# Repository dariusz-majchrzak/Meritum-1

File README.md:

# Meritum-1: Polish 8-bit Home Computer
This repository provides all the files needed to build a **Meritum 1 (Model 1)** ( https://pl.wikipedia.org/wiki/Meritum_(komputer) ) hardware recreation, closely following the design of the first microcomputer to be mass‑produced in Poland.<br>

Production of the Meritum computer began in mid‑1983, and its architecture was based on a design similar to the TRS‑80 Model I. Across all versions — Meritum I, II, and III — approximately 2,500 units were produced between 1984 and 1986.<br>

It has fascinated me for years as an important part of Poland’s computing history. I never had the chance to see an original unit in person, and my attempts to buy one at auctions quickly ended with prices far beyond reach. 
I also noticed that almost no modern retro‑computing projects related to it exist.

Given that, I decided to build one myself: using the documentation available online — schematics, module descriptions, and board photos — I set out to recreate the machine as my own hardware project.

**Meritum 1 (Model 1)** <br>
Basic Technical Specifications:
* RAM: 16 KB (RAMD) + 1 KB (RAMS)
* ROM: 14 KB (BASIC)
* Video Memory: 1 KB (RAMS)
* Display Modes: Text — 16×64 or 16×32
* Peripherals: serial interface (i8251), parallel interface (i8255), tape interface
* Colors: Monochrome
<br>
As of September 27, 2026, there are 4 successful builds (based on this pcb project), so the design files can be assumed valid.<br>
<br>

Top view of the mainboard:<br>

Side view of the computer with connectors:<br>

Example startup screen:<br>

Important notes:<br>
* Please note that this is a complex hardware project that requires solid technical expertise from anyone who decides to build it.<br>
* While significant care has been taken during the design and verification process, the project may still need additional fixes, especially if the original design included fixes implemented directly at the PCB level that were not reflected in the published schematics.

## PCBs
The clone consists of two separate PCBs:
* [Meritum_PGW](Meritum_PGW) (Meritum Płyta Główna) - is the main board.
* [Meritum_KLT](Meritum_KLT) (Meritum Klawiatura) - is a replacement keyboard that uses standard Cherry MX switches.

## ROMs
Since the licensing status of the ROMs used in the Meritum 1 computer is not clear to me, I have not included them in this repository.<br> 
Below, however, I provide links to a websites where they can be found, along with many other valuable resources:
* https://web.archive.org/web/20201023154655/https://sites.google.com/site/krzkomar/meritum-1
* https://www.planetemu.net/rom/mame-roms-merged/meritum1<br>
  
Many useful materials can also be found at: https://www.speccy.pl/news.php .

## Assembling
Although the mainboard includes several configuration jumpers, it does not require any additional settings that need to be adjusted before powering it on. The default configuration is sufficient.<br>

To connect mainboard with keyboard I have used:
-  single and double Row, 2.54mm straight, Gold PCB Female Sockets Connector
-  single and double Row, 2.54mm straight, Gold PCB Male Pin Header connector (h=29.5mm)
  
More to follow.

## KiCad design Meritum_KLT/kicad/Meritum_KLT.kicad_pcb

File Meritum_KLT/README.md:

# Meritum 1 - keyboard

This part of the project is the clone of the Meritum 1 keyboard.

## Files
This directory contains: 

* [BOM](bom) - Interactive HTML BOM
* [Gerber](gerber) - files (JLCPCB-compatible zip files)
* [IMG](img) - photos of the keyboard
* [KiCAD](kicad) - project design in KiCAD 10
* [Schematic](schematic) - Schematic in PDF format

## Assembling
As for assembling the keyboard PCB, there are no major challenges here. The board is relatively straightforward to build.<br> 
One piece of information may be more important: for mounting the switches I used gold‑plated hot‑swap sockets for mechanical keyboards.
See: [Meritum1_KLT_BOTTOM](img/Meritum1_KLT_BOTTOM.png)

More to follow.

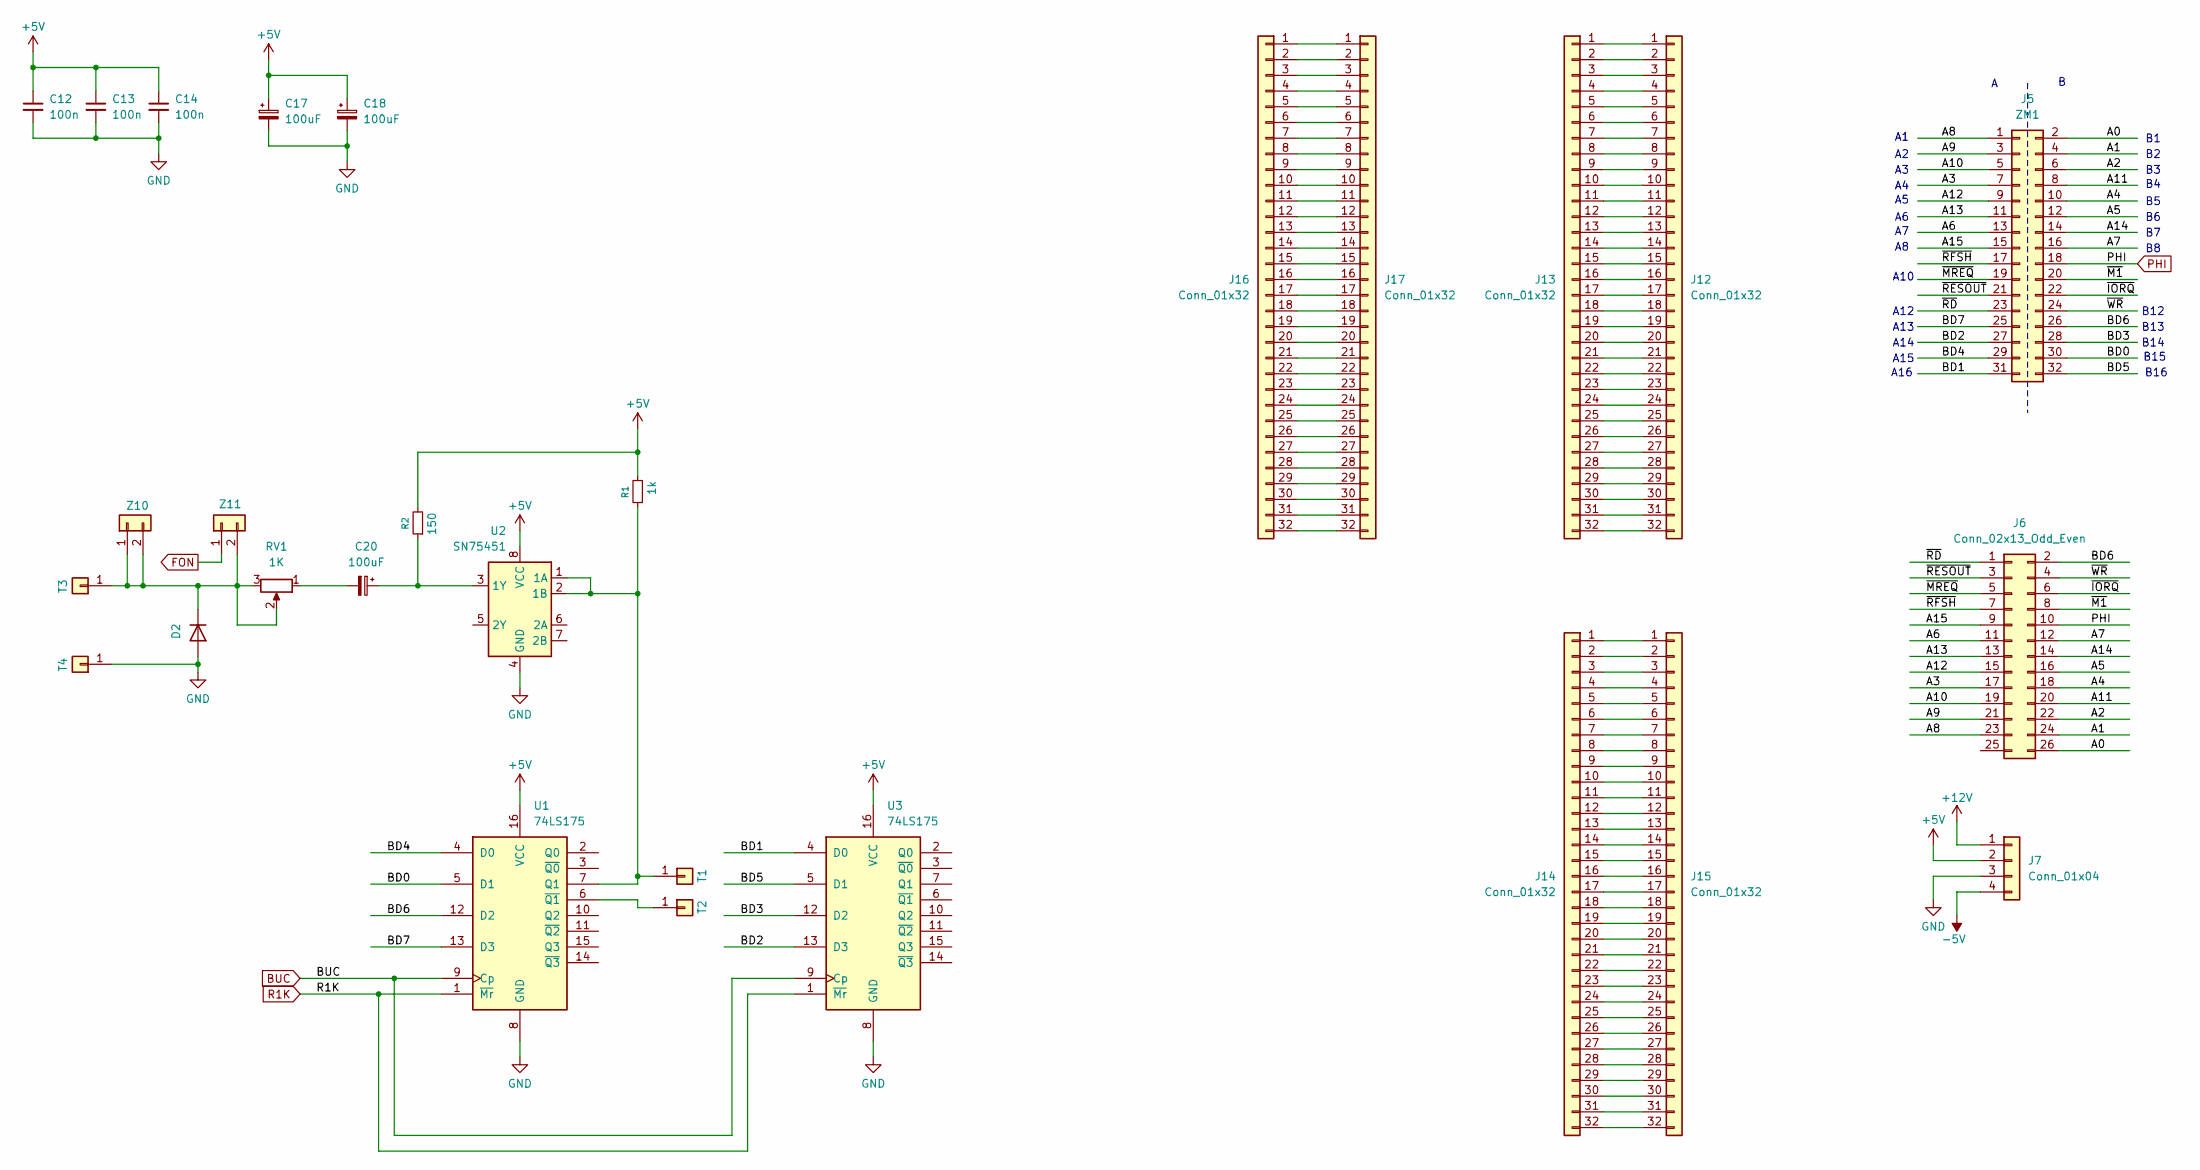
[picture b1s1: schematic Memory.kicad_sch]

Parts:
C12, C13, C14: 100n; C_Rect_L7.0mm_W2.5mm_P5.00mm
C17, C18, C20: 100uF; CP_Radial_D5.0mm_P2.50mm
D2: 1N4148; D_DO-35_SOD27_P7.62mm_Horizontal
J5: ZM1; PinHeader_2x16_P2.54mm_Vertical
J6: Conn_02x13_Odd_Even; PinHeader_2x13_P2.54mm_Vertical
J7: Conn_01x04; PinHeader_1x04_P2.54mm_Vertical
J12, J13, J14, J15, J16, J17: Conn_01x32; PinHeader_1x32_P2.54mm_Vertical
R1: 1k; r_400
R2: 150; r_400
RV1: 1K; Potentiometer_Bourns_3386P_Vertical
T1, T2, T3, T4: T18; pin
U1, U3: 74LS175; DIP-16_W7.62mm_LongPads
U2: SN75451; DIP-8_W7.62mm
Z10, Z11: Conn_01x02; PinHeader_1x02_P2.54mm_Vertical

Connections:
+5V: C12.1, C13.1, C14.1, C17.1, C18.1, J7.2, R1.2, R2.2, U1.16 (VCC), U2.8 (VCC), U3.16 (VCC); also elsewhere on the board
+12V: J7.1; also elsewhere on the board
-5V: J7.4; also elsewhere on the board
/Memory/A0: J5.2, J6.26
/Memory/A1: J5.4, J6.24
/Memory/A2: J5.6, J6.22
/Memory/A3: J5.7, J6.17
/Memory/A4: J5.10, J6.18
/Memory/A5: J5.12, J6.16
/Memory/A6: J5.13, J6.11
/Memory/A7: J5.16, J6.12
/Memory/A8: J5.1, J6.23
/Memory/A9: J5.3, J6.21
/Memory/A10: J5.5, J6.19
/Memory/A11: J5.8, J6.20
/Memory/A12: J5.9, J6.15
/Memory/A13: J5.11, J6.13
/Memory/A14: J5.14, J6.14
/Memory/A15: J5.15, J6.9
/Memory/BD0: J5.30, U1.5 (D1)
/Memory/BD1: J5.31, U3.4 (D0)
/Memory/BD2: J5.27, U3.13 (D3)
/Memory/BD3: J5.28, U3.12 (D2)
/Memory/BD4: J5.29, U1.4 (D0)
/Memory/BD5: J5.32, U3.5 (D1)
/Memory/BD6: J5.26, J6.2, U1.12 (D2)
/Memory/BD7: J5.25, U1.13 (D3)
/Memory/~IORQ: J5.22, J6.6
/Memory/~M1: J5.20, J6.8
/Memory/~MREQ: J5.19, J6.5
/Memory/~RD: J5.23, J6.1
/Memory/~RESOUT: J5.21, J6.3
/Memory/~RFSH: J5.17, J6.7
/Memory/~WR: J5.24, J6.4
BUC: U1.9 (Cp), U3.9 (Cp); also elsewhere on the board
FON: Z11.1; also elsewhere on the board
GND: C12.2, C13.2, C14.2, C17.2, C18.2, D2.2 (A), J7.3, T4.1 (Pin_1_1), U1.8 (GND), U2.4 (GND), U3.8 (GND); also elsewhere on the board
unnamed: C20.2, RV1.1
unnamed: D2.1 (K), RV1.2, RV1.3, T3.1 (Pin_1_1), Z10.1, Z10.2, Z11.2
unnamed: J12.1, J13.1
unnamed: J12.2, J13.2
unnamed: J12.3, J13.3
unnamed: J12.4, J13.4
unnamed: J12.5, J13.5
unnamed: J12.6, J13.6
unnamed: J12.7, J13.7
unnamed: J12.8, J13.8
unnamed: J12.9, J13.9
unnamed: J12.10, J13.10
unnamed: J12.11, J13.11
unnamed: J12.12, J13.12
unnamed: J12.13, J13.13
unnamed: J12.14, J13.14
unnamed: J12.15, J13.15
unnamed: J12.16, J13.16
unnamed: J12.17, J13.17
unnamed: J12.18, J13.18
unnamed: J12.19, J13.19
unnamed: J12.20, J13.20
unnamed: J12.21, J13.21
unnamed: J12.22, J13.22
unnamed: J12.23, J13.23
unnamed: J12.24, J13.24
unnamed: J12.25, J13.25
unnamed: J12.26, J13.26
unnamed: J12.27, J13.27
unnamed: J12.28, J13.28
unnamed: J12.29, J13.29
unnamed: J12.30, J13.30
unnamed: J12.31, J13.31
unnamed: J12.32, J13.32
unnamed: J14.1, J15.1
unnamed: J14.2, J15.2
unnamed: J14.3, J15.3
unnamed: J14.4, J15.4
unnamed: J14.5, J15.5
unnamed: J14.6, J15.6
unnamed: J14.7, J15.7
unnamed: J14.8, J15.8
unnamed: J14.9, J15.9
unnamed: J14.10, J15.10
unnamed: J14.11, J15.11
unnamed: J14.12, J15.12
unnamed: J14.13, J15.13
unnamed: J14.14, J15.14
unnamed: J14.15, J15.15
unnamed: J14.16, J15.16
unnamed: J14.17, J15.17
unnamed: J14.18, J15.18
unnamed: J14.19, J15.19
unnamed: J14.20, J15.20
unnamed: J14.21, J15.21
unnamed: J14.22, J15.22
unnamed: J14.23, J15.23
unnamed: J14.24, J15.24
unnamed: J14.25, J15.25
unnamed: J14.26, J15.26
unnamed: J14.27, J15.27
unnamed: J14.28, J15.28
unnamed: J14.29, J15.29
unnamed: J14.30, J15.30
unnamed: J14.31, J15.31
unnamed: J14.32, J15.32
unnamed: J16.1, J17.1
unnamed: J16.2, J17.2
unnamed: J16.3, J17.3
unnamed: J16.4, J17.4
unnamed: J16.5, J17.5
unnamed: J16.6, J17.6
unnamed: J16.7, J17.7
unnamed: J16.8, J17.8
unnamed: J16.9, J17.9
unnamed: J16.10, J17.10
unnamed: J16.11, J17.11
unnamed: J16.12, J17.12
unnamed: J16.13, J17.13
unnamed: J16.14, J17.14
unnamed: J16.15, J17.15
unnamed: J16.16, J17.16
unnamed: J16.17, J17.17
unnamed: J16.18, J17.18
unnamed: J16.19, J17.19
unnamed: J16.20, J17.20
unnamed: J16.21, J17.21
unnamed: J16.22, J17.22
unnamed: J16.23, J17.23
unnamed: J16.24, J17.24
unnamed: J16.25, J17.25
unnamed: J16.26, J17.26
unnamed: J16.27, J17.27
unnamed: J16.28, J17.28
unnamed: J16.29, J17.29
unnamed: J16.30, J17.30
unnamed: J16.31, J17.31
unnamed: J16.32, J17.32
unnamed: R1.1, T1.1 (Pin_1_1), U1.7 (Q1), U2.1 (1A), U2.2 (1B)
unnamed: T2.1 (Pin_1_1), U1.6 (~Q1)
unnamed: C20.1, R2.1, U2.3 (1Y)
PHI: J5.18, J6.10
R1K: U1.1 (~Mr), U3.1 (~Mr); also elsewhere on the board

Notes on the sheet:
B13
B12
A16
B15
A15
B16
A14
A13
A10
A12
B14

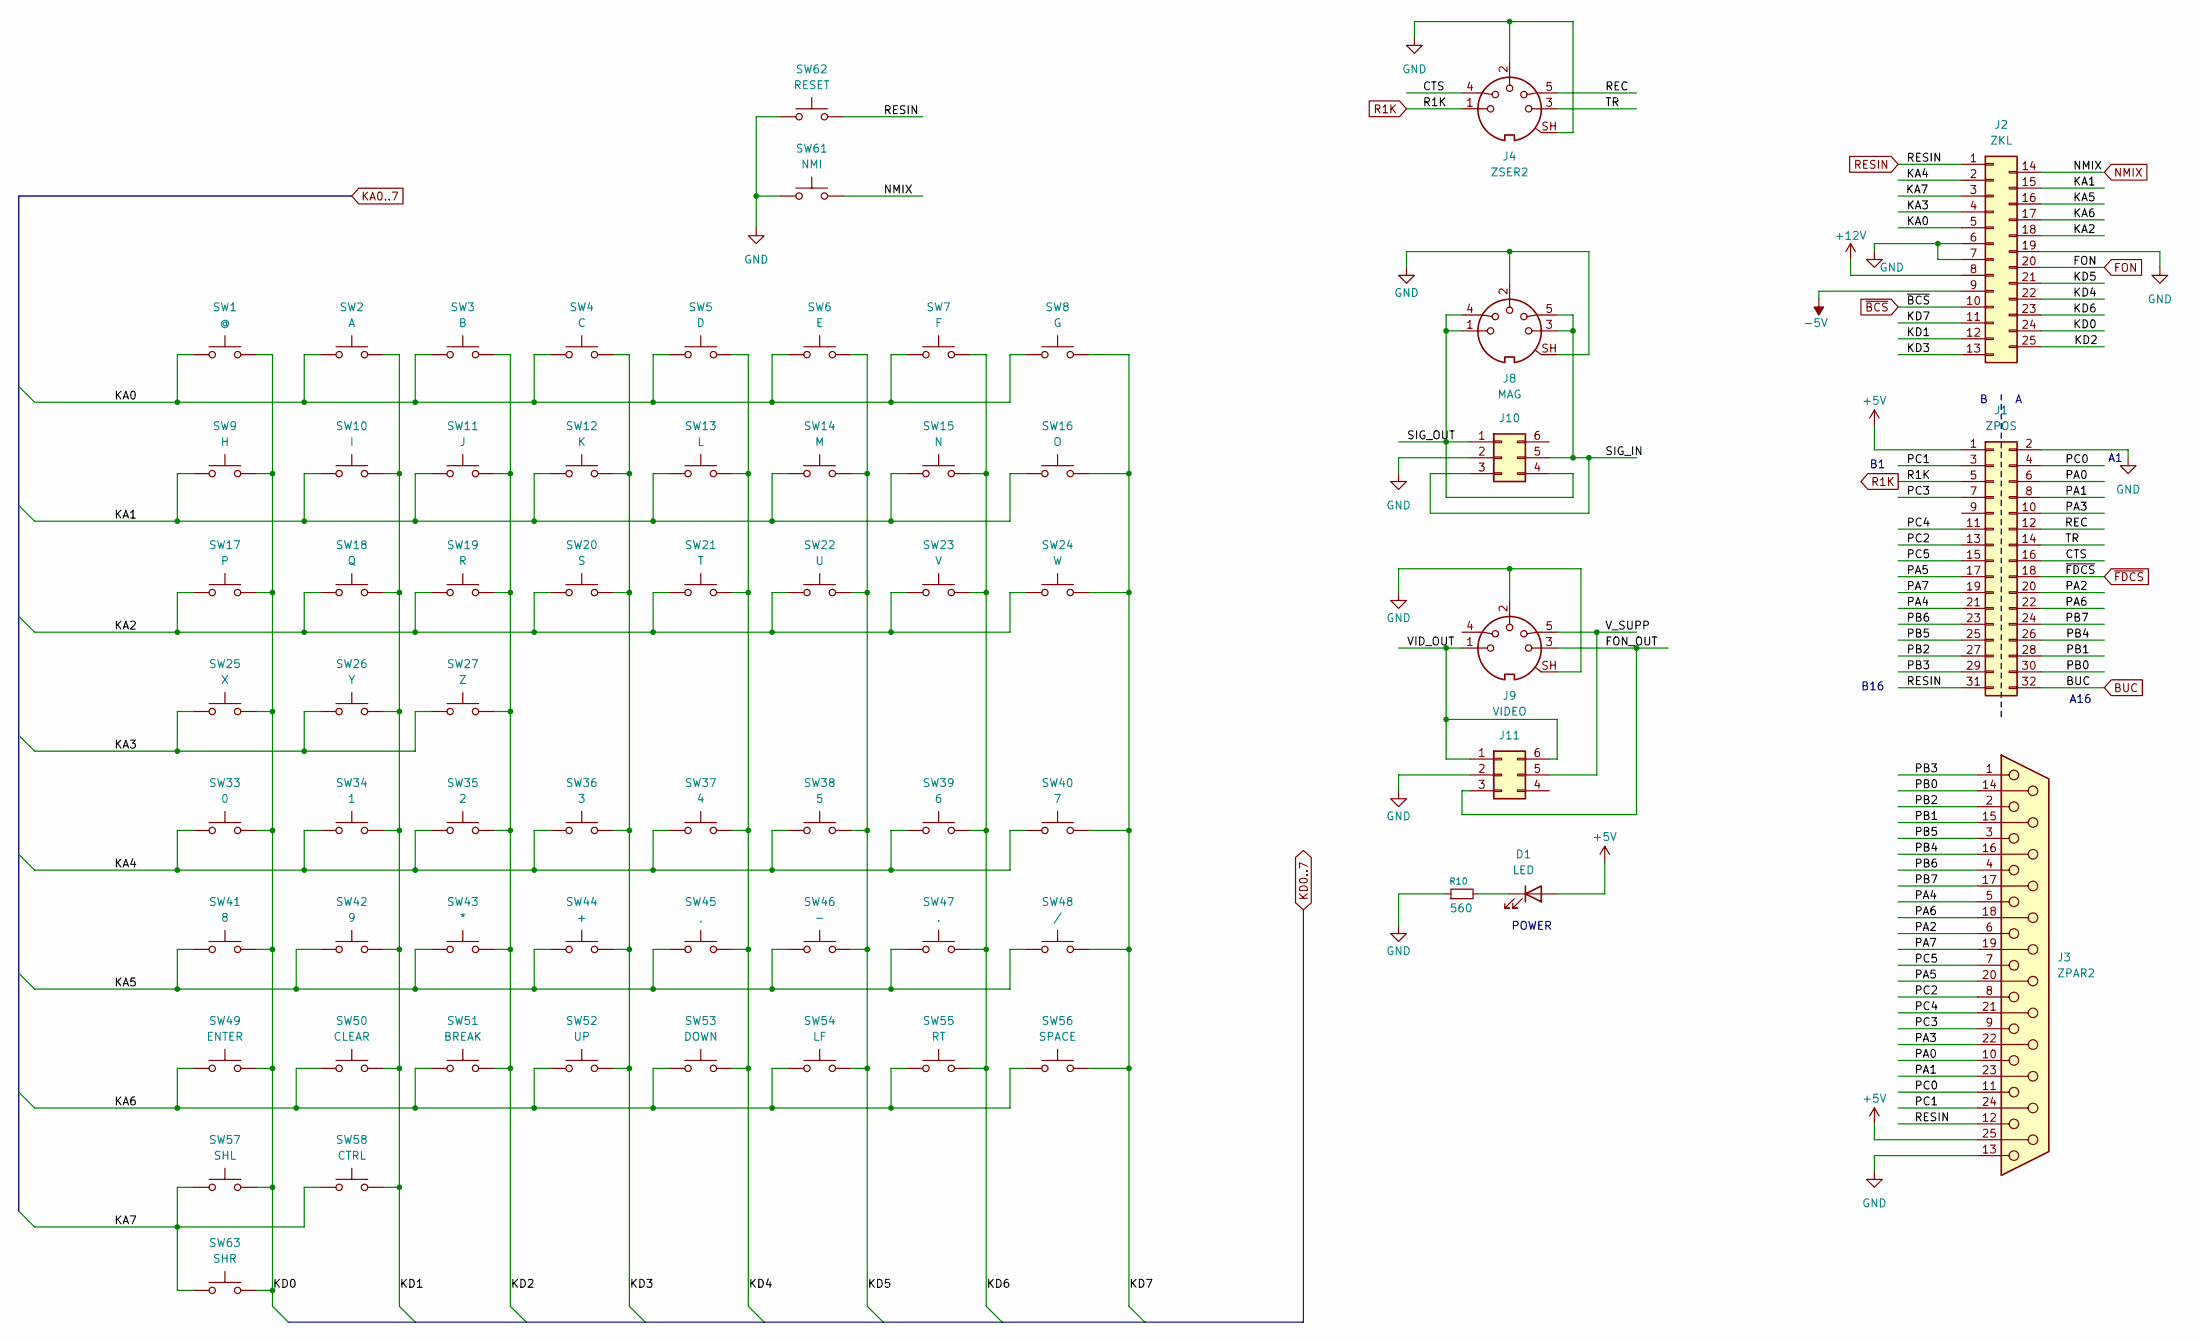
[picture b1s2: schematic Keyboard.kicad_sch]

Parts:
D1: LED; LED_D5.0mm
J1: ZPOS; PinHeader_2x16_P2.54mm_Vertical
J2: ZKL; PinSocket_25_P2.54mm_Vertical
J3: ZPAR2; DSUB-25_Socket_Horizontal_P2.77x2.84mm_EdgePinOffset7.70mm_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
J4: ZSER2; CUI_SDS-50J
J8: MAG; CUI_SDS-50J
J9: VIDEO; CUI_SDS-50J
J10, J11: Conn_02x03_Counter_Clockwise; PinHeader_2x03_P2.54mm_Vertical
R10: 560; r_400
SW1: @; SW_Cherry_MX_1.00u_PCB
SW2: A; SW_Cherry_MX_1.00u_PCB
SW3: B; SW_Cherry_MX_1.00u_PCB
SW4: C; SW_Cherry_MX_1.00u_PCB
SW5: D; SW_Cherry_MX_1.00u_PCB
SW6: E; SW_Cherry_MX_1.00u_PCB
SW7: F; SW_Cherry_MX_1.00u_PCB
SW8: G; SW_Cherry_MX_1.00u_PCB
SW9: H; SW_Cherry_MX_1.00u_PCB
SW10: I; SW_Cherry_MX_1.00u_PCB
SW11: J; SW_Cherry_MX_1.00u_PCB
SW12: K; SW_Cherry_MX_1.00u_PCB
SW13: L; SW_Cherry_MX_1.00u_PCB
SW14: M; SW_Cherry_MX_1.00u_PCB
SW15: N; SW_Cherry_MX_1.00u_PCB
SW16: O; SW_Cherry_MX_1.00u_PCB
SW17: P; SW_Cherry_MX_1.00u_PCB
SW18: Q; SW_Cherry_MX_1.00u_PCB
SW19: R; SW_Cherry_MX_1.00u_PCB
SW20: S; SW_Cherry_MX_1.00u_PCB
SW21: T; SW_Cherry_MX_1.00u_PCB
SW22: U; SW_Cherry_MX_1.00u_PCB
SW23: V; SW_Cherry_MX_1.00u_PCB
SW24: W; SW_Cherry_MX_1.00u_PCB
SW25: X; SW_Cherry_MX_1.00u_PCB
SW26: Y; SW_Cherry_MX_1.00u_PCB
SW27: Z; SW_Cherry_MX_1.00u_PCB
SW33: 0; SW_Cherry_MX_1.00u_PCB
SW34: 1; SW_Cherry_MX_1.00u_PCB
SW35: 2; SW_Cherry_MX_1.00u_PCB
SW36: 3; SW_Cherry_MX_1.00u_PCB
SW37: 4; SW_Cherry_MX_1.00u_PCB
SW38: 5; SW_Cherry_MX_1.00u_PCB
SW39: 6; SW_Cherry_MX_1.00u_PCB
SW40: 7; SW_Cherry_MX_1.00u_PCB
SW41: 8; SW_Cherry_MX_1.00u_PCB
SW42: 9; SW_Cherry_MX_1.00u_PCB
SW43: *; SW_Cherry_MX_1.00u_PCB
SW44: +; SW_Cherry_MX_1.00u_PCB
SW45: ,; SW_Cherry_MX_1.00u_PCB
SW46: -; SW_Cherry_MX_1.00u_PCB
SW47: .; SW_Cherry_MX_1.00u_PCB
SW48: /; SW_Cherry_MX_1.00u_PCB
SW49: ENTER; SW_Cherry_MX_1.50u_PCB
SW50: CLEAR; SW_Cherry_MX_1.00u_PCB
SW51: BREAK; SW_Cherry_MX_1.00u_PCB
SW52: UP; SW_Cherry_MX_1.00u_PCB
SW53: DOWN; SW_Cherry_MX_1.00u_PCB
SW54: LF; SW_Cherry_MX_1.00u_PCB
SW55: RT; SW_Cherry_MX_1.00u_PCB
SW56: SPACE; SW_Cherry_MX_6.25u_PCB
SW57: SHL; SW_Cherry_MX_1.00u_PCB
SW58: CTRL; SW_Cherry_MX_1.50u_PCB
SW61: NMI; SW_Cherry_MX_1.00u_PCB
SW62: RESET; SW_Push_2P2T_Toggle_CK_PVA2OAH5xxxxxxV2
SW63: SHR; SW_Cherry_MX_1.00u_PCB

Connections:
+5V: D1.2 (A), J1.1, J3.25; also elsewhere on the board
+12V: J2.8; also elsewhere on the board
-5V: J2.9; also elsewhere on the board
/Keyboard/CTS: J1.16, J4.4
/Keyboard/FON_OUT: J9.3, J11.3
/Keyboard/KA0: J2.5, SW1.1, SW2.1, SW3.1, SW4.1, SW5.1, SW6.1, SW7.1, SW8.1
/Keyboard/KA1: J2.15, SW9.1, SW10.1, SW11.1, SW12.1, SW13.1, SW14.1, SW15.1, SW16.1
/Keyboard/KA2: J2.18, SW17.1, SW18.1, SW19.1, SW20.1, SW21.1, SW22.1, SW23.1, SW24.1
/Keyboard/KA3: J2.4, SW25.1, SW26.1, SW27.1
/Keyboard/KA4: J2.2, SW33.1, SW34.1, SW35.1, SW36.1, SW37.1, SW38.1, SW39.1, SW40.1
/Keyboard/KA5: J2.16, SW41.1, SW42.1, SW43.1, SW44.1, SW45.1, SW46.1, SW47.1, SW48.1
/Keyboard/KA6: J2.17, SW49.1, SW50.1, SW51.1, SW52.1, SW53.1, SW54.1, SW55.1, SW56.1
/Keyboard/KA7: J2.3, SW57.1, SW58.1, SW63.1
/Keyboard/KD0: J2.24, SW1.2, SW9.2, SW17.2, SW25.2, SW33.2, SW41.2, SW49.2, SW57.2, SW63.2
/Keyboard/KD1: J2.12, SW2.2, SW10.2, SW18.2, SW26.2, SW34.2, SW42.2, SW50.2, SW58.2
/Keyboard/KD2: J2.25, SW3.2, SW11.2, SW19.2, SW27.2, SW35.2, SW43.2, SW51.2
/Keyboard/KD3: J2.13, SW4.2, SW12.2, SW20.2, SW36.2, SW44.2, SW52.2
/Keyboard/KD4: J2.22, SW5.2, SW13.2, SW21.2, SW37.2, SW45.2, SW53.2
/Keyboard/KD5: J2.21, SW6.2, SW14.2, SW22.2, SW38.2, SW46.2, SW54.2
/Keyboard/KD6: J2.23, SW7.2, SW15.2, SW23.2, SW39.2, SW47.2, SW55.2
/Keyboard/KD7: J2.11, SW8.2, SW16.2, SW24.2, SW40.2, SW48.2, SW56.2
/Keyboard/PA0: J1.6, J3.10
/Keyboard/PA1: J1.8, J3.23
/Keyboard/PA2: J1.20, J3.6
/Keyboard/PA3: J1.10, J3.22
/Keyboard/PA4: J1.21, J3.5
/Keyboard/PA5: J1.17, J3.20
/Keyboard/PA6: J1.22, J3.18
/Keyboard/PA7: J1.19, J3.19
/Keyboard/PB0: J1.30, J3.14
/Keyboard/PB1: J1.28, J3.15
/Keyboard/PB2: J1.27, J3.2
/Keyboard/PB3: J1.29, J3.1
/Keyboard/PB4: J1.26, J3.16
/Keyboard/PB5: J1.25, J3.3
/Keyboard/PB6: J1.23, J3.4
/Keyboard/PB7: J1.24, J3.17
/Keyboard/PC0: J1.4, J3.11
/Keyboard/PC1: J1.3, J3.24
/Keyboard/PC2: J1.13, J3.8
/Keyboard/PC3: J1.7, J3.9
/Keyboard/PC4: J1.11, J3.21
/Keyboard/PC5: J1.15, J3.7
/Keyboard/REC: J1.12, J4.5
/Keyboard/SIG_IN: J8.3, J8.5, J10.3, J10.5
/Keyboard/SIG_OUT: J8.1, J8.4, J10.1, J10.4
/Keyboard/TR: J1.14, J4.3
/Keyboard/VID_OUT: J9.1, J11.1, J11.6
/Keyboard/V_SUPP: J9.5, J11.5
BUC: J1.32; also elsewhere on the board
FON: J2.20; also elsewhere on the board
GND: J1.2, J2.6, J2.7, J2.19, J3.13, J4.2, J4.SH, J8.2, J8.SH, J9.2, J9.SH, J10.2, J11.2, R10.1, SW61.1, SW62.1; also elsewhere on the board
NMIX: J2.14, SW61.2
unnamed: D1.1 (K), R10.2
R1K: J1.5, J4.1; also elsewhere on the board
RESIN: J1.31, J2.1, J3.12, SW62.2
~BCS: J2.10
~FDCS: J1.18

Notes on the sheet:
POWER
B16
A16

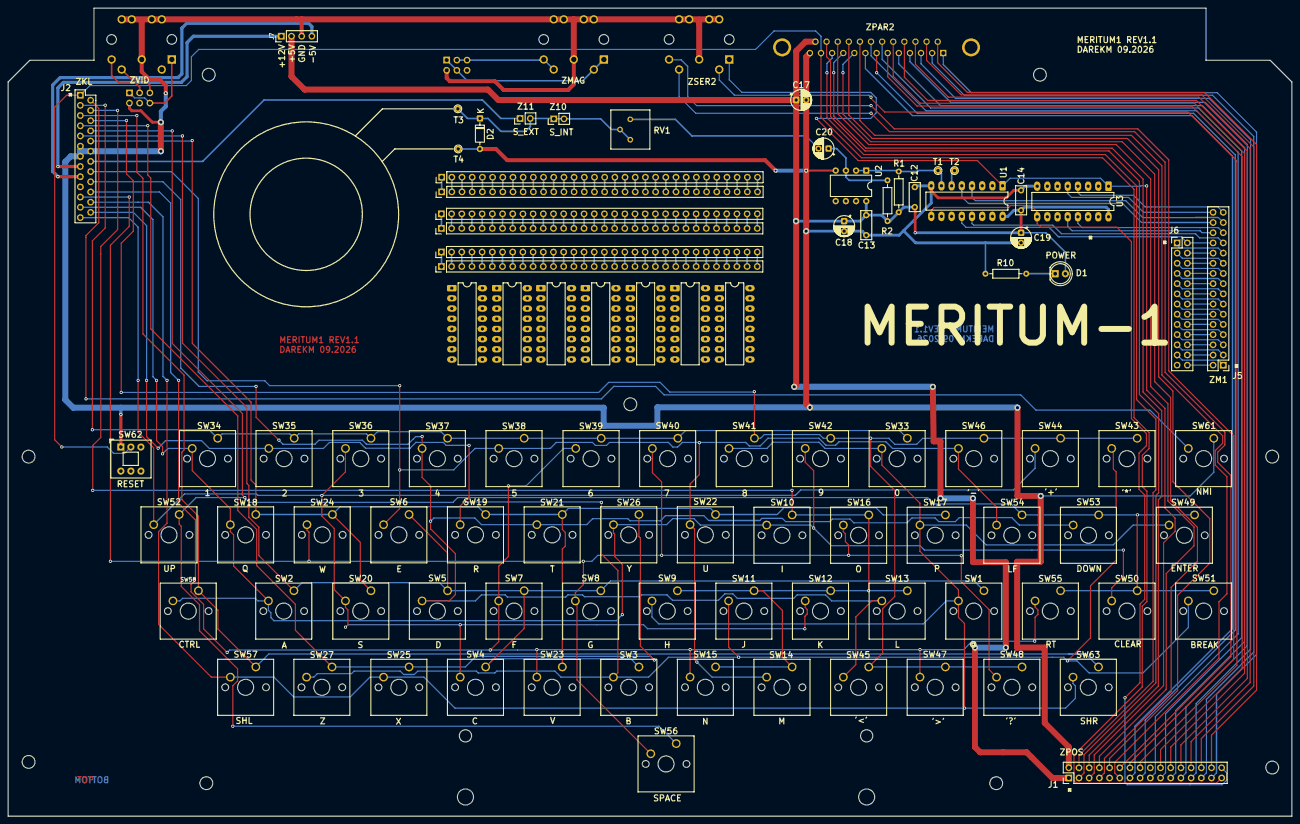
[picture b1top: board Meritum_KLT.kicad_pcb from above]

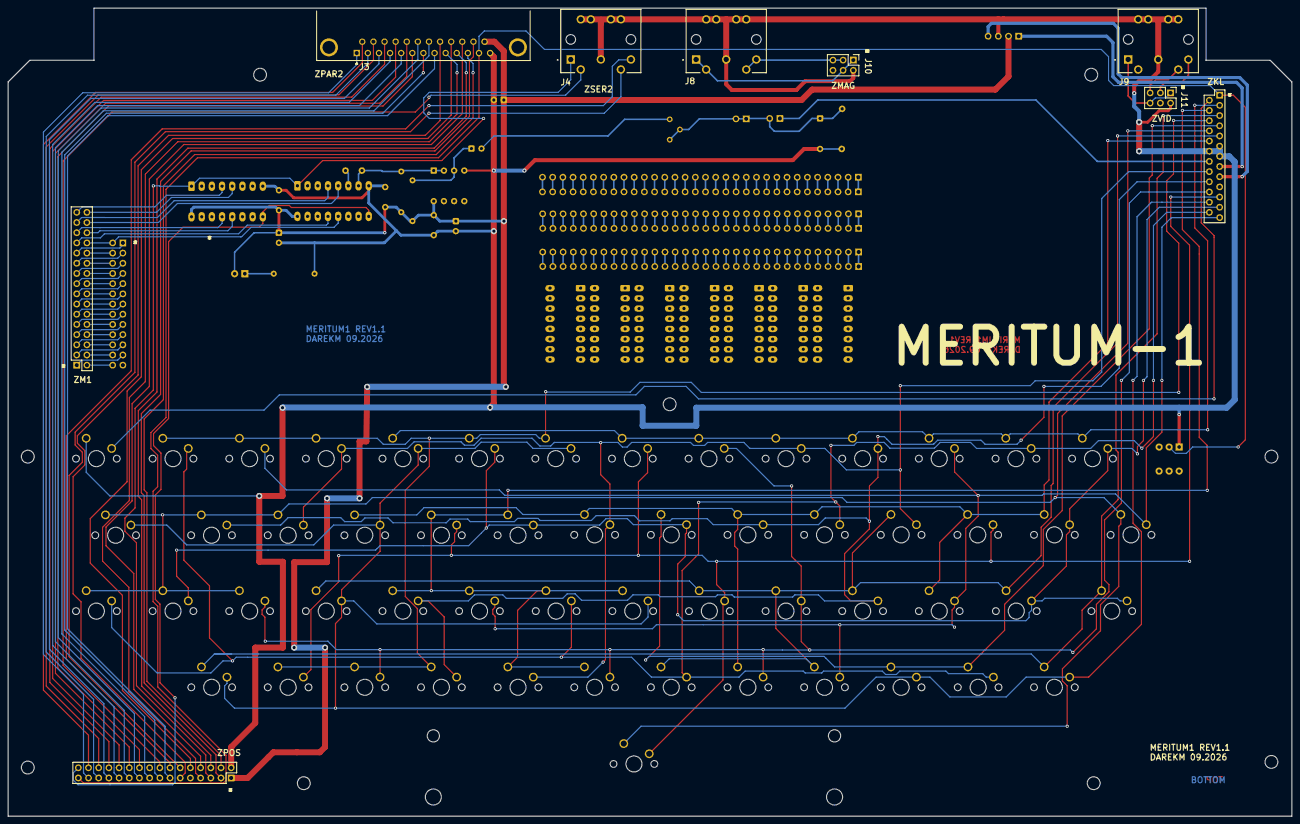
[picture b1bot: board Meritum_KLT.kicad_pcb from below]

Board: 2 copper layers, 320.0 x 201.4 mm, 95 parts (6 on the bottom side), 189 nets.

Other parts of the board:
C19: 100uF; CP_Radial_D5.0mm_P2.50mm

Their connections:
+5V: C19.1; also elsewhere on the board
GND: C19.2; also elsewhere on the board
